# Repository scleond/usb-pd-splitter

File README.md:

# USB-PD Splitter

A KiCad 10 design for a passive USB-C power/data injector: a dedicated USB-C
power input and a separate USB 2.0 data input feed one USB-C device output.

## At a glance

- `PWR_IN` supplies `VBUS`, `GND`, and CC signaling to `OUT`.
- `DATA_IN` supplies USB 2.0 `D+`, `D-`, and `GND` to `OUT`; its `VBUS` is
  isolated from the power path.
- `OUT` is the powered device connection.

This board has no USB-PD controller, data repeater, or role-switching circuit.
Its behavior must be validated with the intended power source, host, and device.

## Repository

- `usb-pd-splitter.kicad_pro`, `.kicad_sch`, and `.kicad_pcb` — KiCad sources
- `usb-pd-splitter.kicad_jobset` — native KiCad validation/export jobset
- `hardware/` — project-local symbols, footprints, and 3D models
- `automation/` — reproducible release CLI and unit tests
- `bom/` — reviewed, human-readable BOM snapshot
- `manufacturing/` — fabrication profile and release templates

Generated review and release artifacts belong in `outputs/` and `dist/`; they
are not source files.

## Documentation

- [Design notes](docs/DESIGN.md) — topology and operating assumptions
- [Requirements](docs/requirements.md) — intended interfaces and constraints
- [Connector mapping](docs/connector-mapping.md) — power, data, and CC paths
- [Release checklist](docs/manufacturing/release-process.md) — required release steps
- [Manufacturing tooling decisions](docs/manufacturing/tooling-decisions.md) — release architecture and boundaries
- [BOM guidance](bom/README.md) — tracked snapshot policy

## Release quick start

Install KiCad 10, make `kicad-cli` available on `PATH`, and install `uv`. After
changing fitted parts, refresh the snapshot and run the preflight:

```powershell
uv run --project automation hwrelease export-bom
uv run --project automation hwrelease validate
```

The formal build, JLCPCB draft placement review, packaging, tagging, and draft
publication process is documented in the [release checklist](docs/manufacturing/release-process.md).
No repository command places an order.

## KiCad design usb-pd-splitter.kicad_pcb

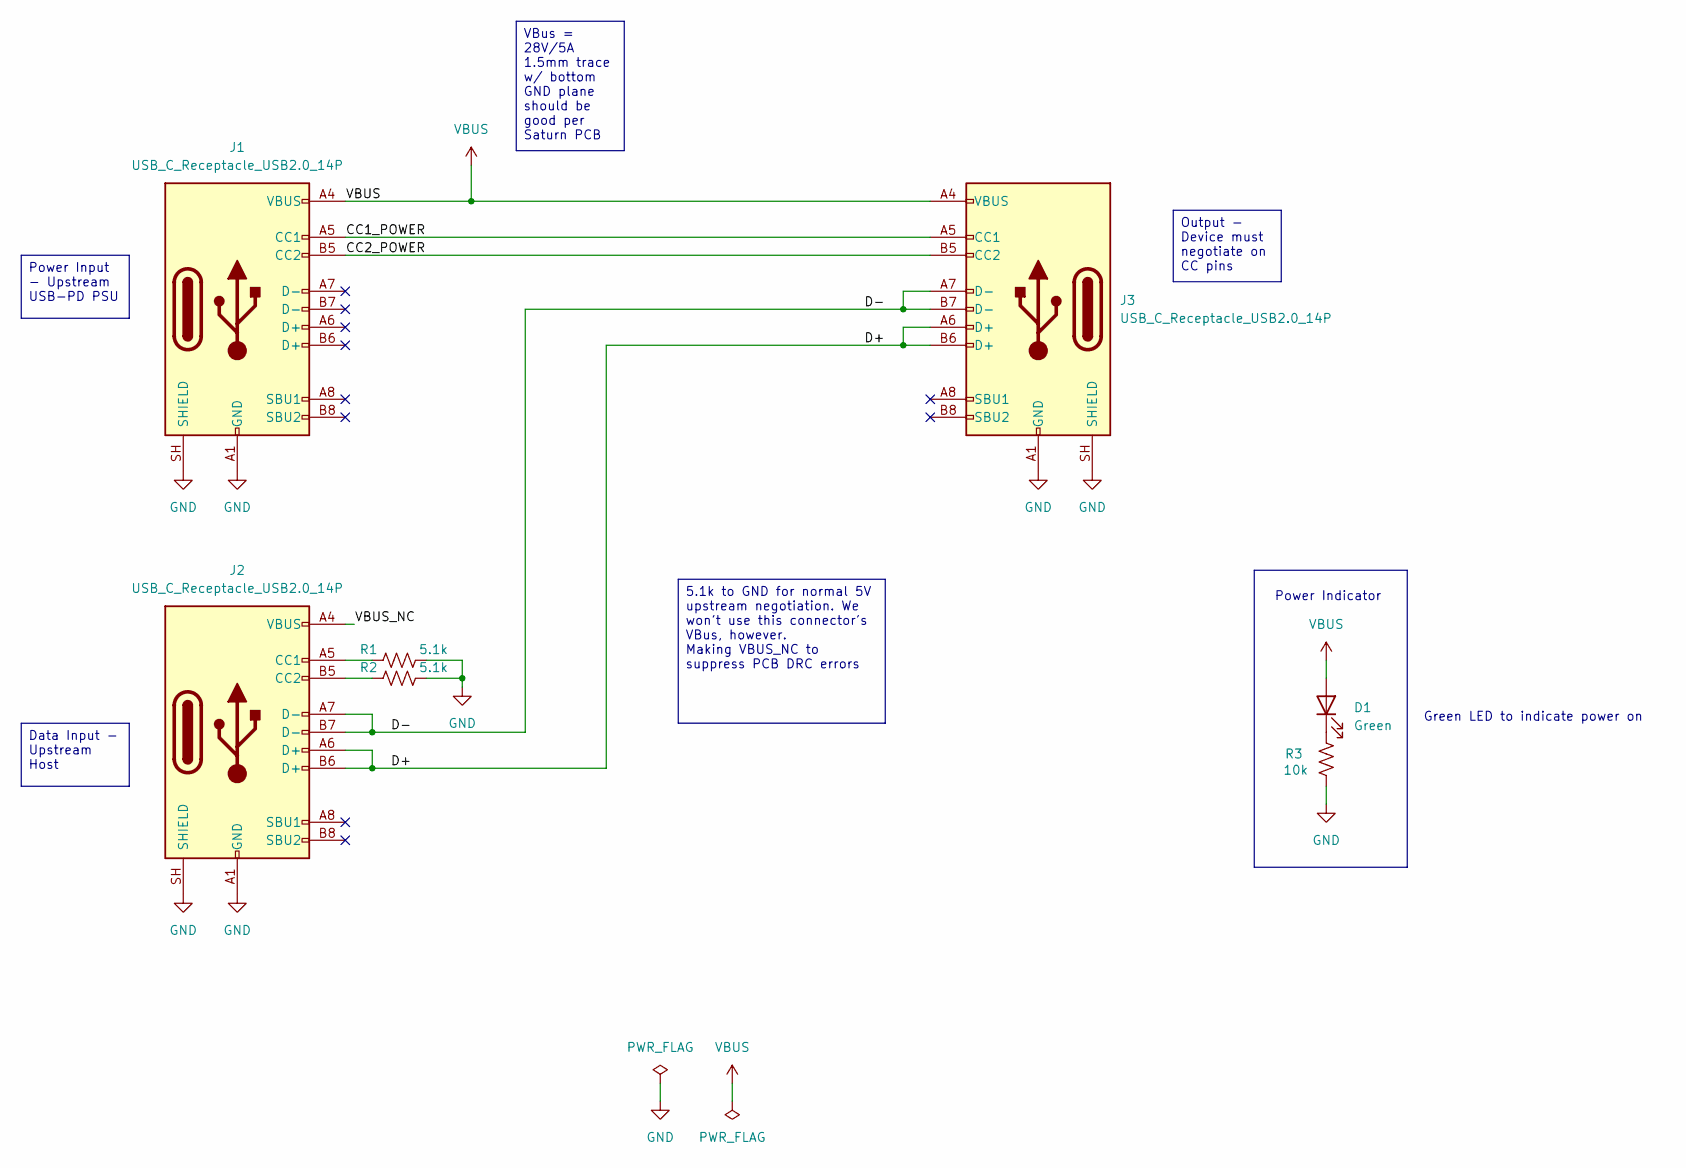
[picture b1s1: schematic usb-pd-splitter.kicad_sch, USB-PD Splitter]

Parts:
D1: Green; LED_0805_2012Metric; MPN NCD0805C1; LCSC Part # C84257
J1, J2, J3: USB_C_Receptacle_USB2.0_14P; USB_C_Receptacle_GCT_USB4110; MPN USB4110-GF-A; LCSC Part # C5143397
R1, R2: 5.1k; R_0805_2012Metric_Pad1.20x1.40mm_HandSolder; MPN 0805W8F5101T5E; LCSC Part # C27834
R3: 10k; R_0805_2012Metric_Pad1.20x1.40mm_HandSolder; MPN 0805W8F1002T5E; LCSC Part # C17414

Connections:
/CC1_POWER: J1.A5 (CC1), J3.A5 (CC1)
/CC2_POWER: J1.B5 (CC2), J3.B5 (CC2)
/D+: J2.A6 (D+), J2.B6 (D+), J3.A6 (D+), J3.B6 (D+)
/D-: J2.A7 (D-), J2.B7 (D-), J3.A7 (D-), J3.B7 (D-)
/VBUS_NC: J2.A4 (VBUS), J2.A9 (VBUS), J2.B4 (VBUS), J2.B9 (VBUS)
GND: J1.A1 (GND), J1.A12 (GND), J1.B1 (GND), J1.B12 (GND), J1.SH (SHIELD), J2.A1 (GND), J2.A12 (GND), J2.B1 (GND), J2.B12 (GND), J2.SH (SHIELD), J3.A1 (GND), J3.A12 (GND), J3.B1 (GND), J3.B12 (GND), J3.SH (SHIELD), R1.1, R2.1, R3.2
unnamed: D1.1 (K), R3.1
unnamed: J2.A5 (CC1), R1.2
unnamed: J2.B5 (CC2), R2.2
VBUS: D1.2 (A), J1.A4 (VBUS), J1.A9 (VBUS), J1.B4 (VBUS), J1.B9 (VBUS), J3.A4 (VBUS), J3.A9 (VBUS), J3.B4 (VBUS), J3.B9 (VBUS)

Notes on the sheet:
Power Indicator
Green LED to indicate power on
Output - Device must negotiate on CC pins
Data Input - Upstream Host
Power Input - Upstream USB-PD PSU
VBus = 28V/5A 1.5mm trace w/ bottom GND plane should be good per Saturn PCB
5.1k to GND for normal 5V upstream negotiation. We won't use this connector's VBus, however. Making VBUS_NC to suppress PCB DRC errors

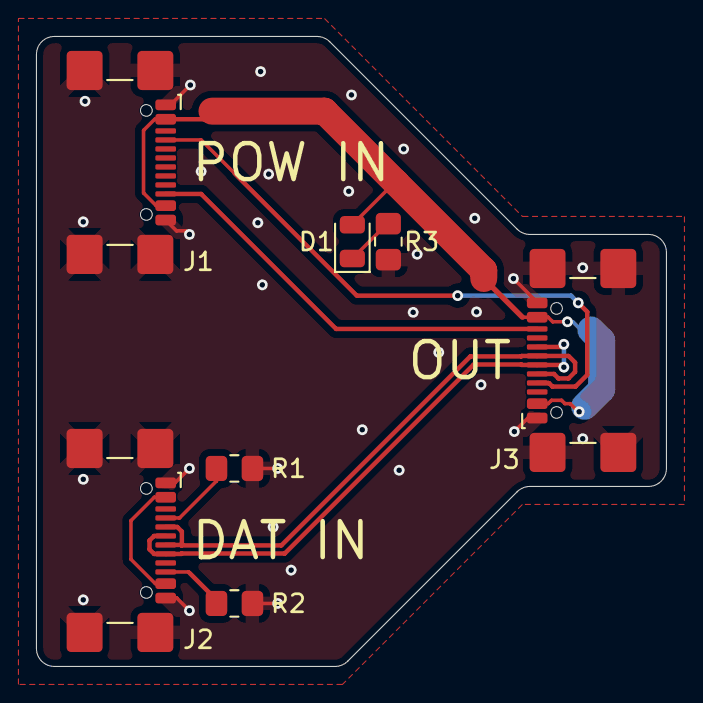
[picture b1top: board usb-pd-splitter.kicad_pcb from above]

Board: 2 copper layers, 35.0 x 35.0 mm, 7 parts (0 on the bottom side), 10 nets.
